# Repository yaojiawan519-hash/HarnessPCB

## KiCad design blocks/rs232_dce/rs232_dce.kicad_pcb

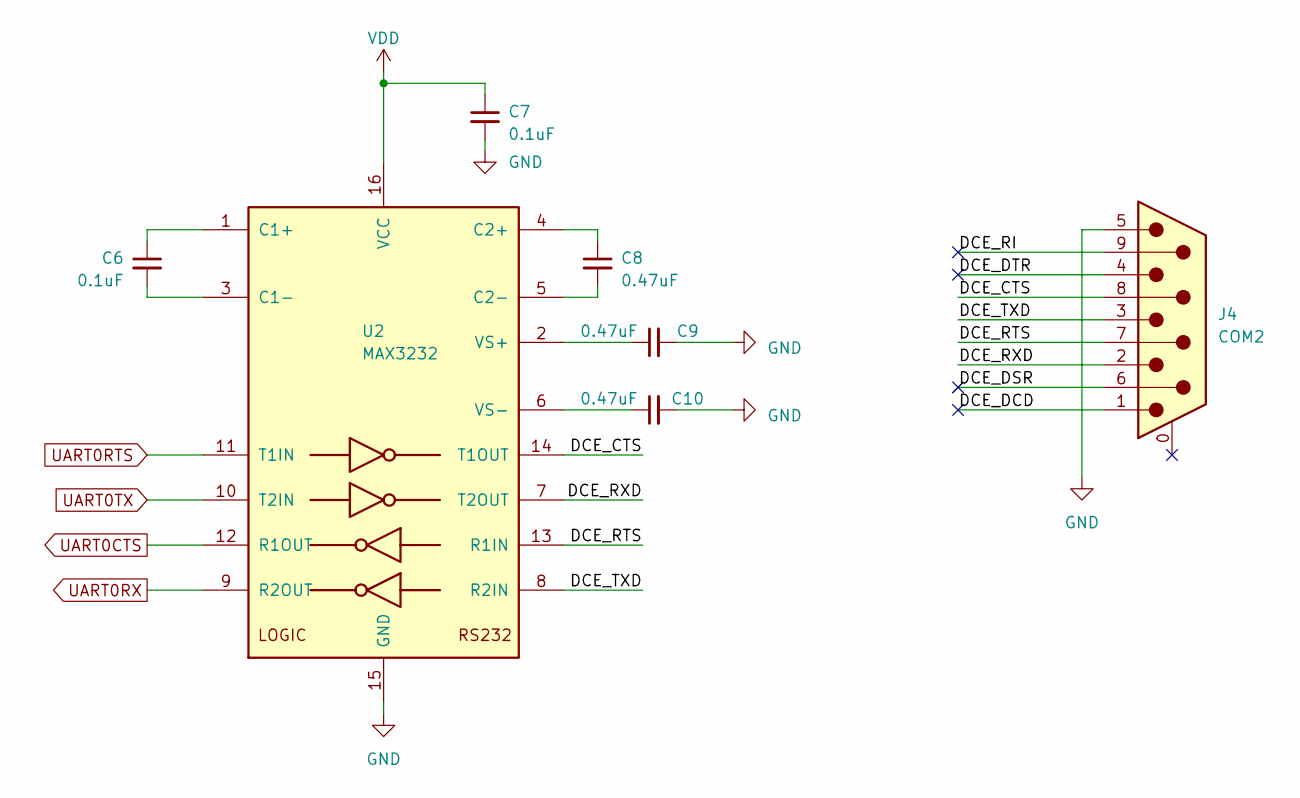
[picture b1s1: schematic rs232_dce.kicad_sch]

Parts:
C6, C7: 0.1uF; C_0805_2012Metric
C8, C9, C10: 0.47uF; C_0805_2012Metric
J4: COM2; DSUB-9_Female_Horizontal_P2.77x2.84mm_EdgePinOffset7.70mm_H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
U2: MAX3232; SOP-16_3.9x9.9mm_P1.27mm

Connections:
/DCE_CTS: J4.8, U2.14 (T1OUT)
/DCE_DCD: J4.1
/DCE_DSR: J4.6
/DCE_DTR: J4.4
/DCE_RI: J4.9
/DCE_RTS: J4.7, U2.13 (R1IN)
/DCE_RXD: J4.2, U2.7 (T2OUT)
/DCE_TXD: J4.3, U2.8 (R2IN)
GND: C7.2, C9.2, C10.2, J4.5, U2.15 (GND)
unnamed: C6.1, U2.1 (C1+)
unnamed: C6.2, U2.3 (C1-)
unnamed: C8.1, U2.4 (C2+)
unnamed: C8.2, U2.5 (C2-)
unnamed: C9.1, U2.2 (VS+)
unnamed: C10.1, U2.6 (VS-)
UART0CTS: U2.12 (R1OUT)
UART0RTS: U2.11 (T1IN)
UART0RX: U2.9 (R2OUT)
UART0TX: U2.10 (T2IN)
VOUT: C7.1, U2.16 (VCC)

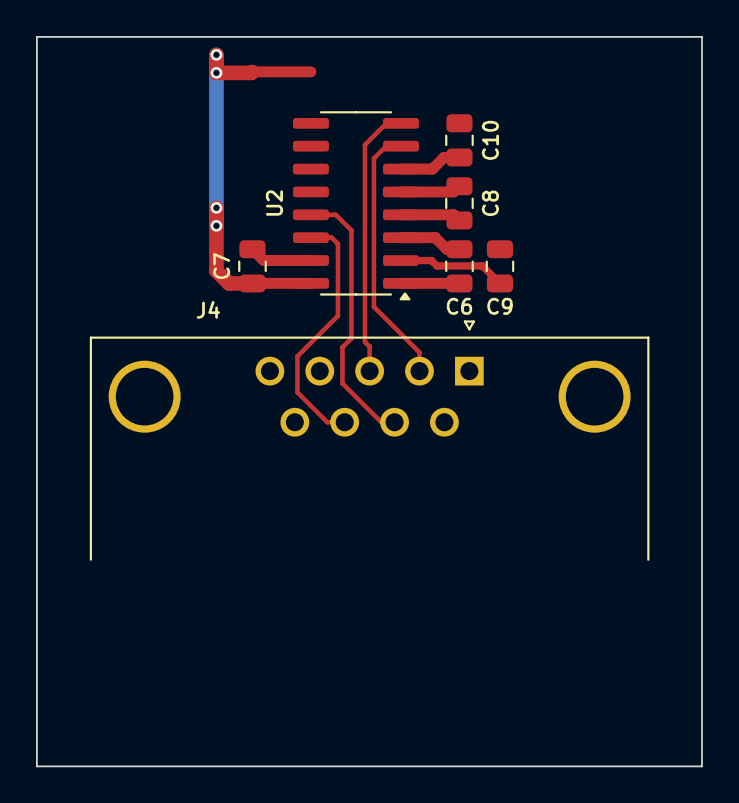
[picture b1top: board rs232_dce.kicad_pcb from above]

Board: 2 copper layers, 37.0 x 40.5 mm, 7 parts (0 on the bottom side), 12 nets.

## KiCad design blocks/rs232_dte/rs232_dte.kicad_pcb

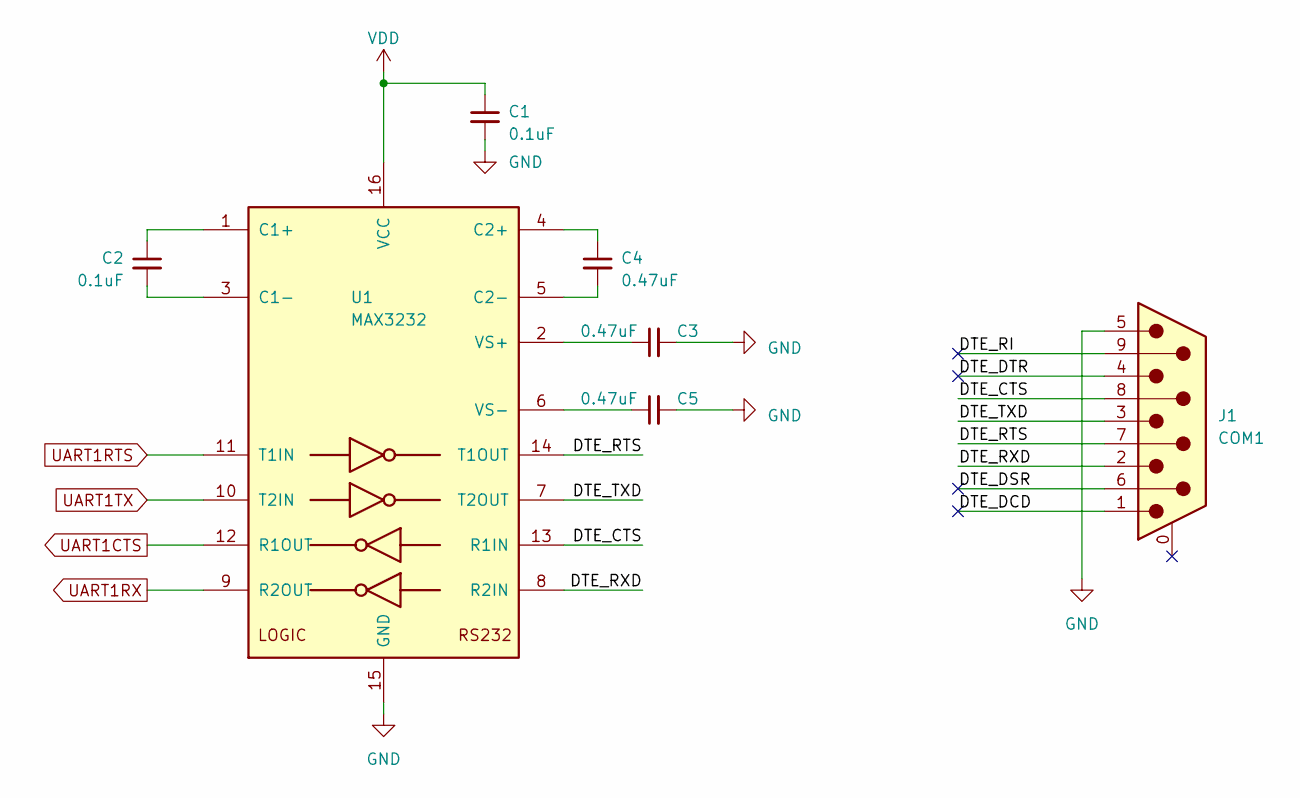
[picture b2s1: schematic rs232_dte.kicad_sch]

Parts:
C1, C2: 0.1uF; C_0805_2012Metric
C3, C4, C5: 0.47uF; C_0805_2012Metric
J1: COM1; DSUB-9_Male_Horizontal_P2.77x2.84mm_EdgePinOffset7.70mm_Hou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
U1: MAX3232; SOP-16_3.9x9.9mm_P1.27mm

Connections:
/DTE_CTS: J1.8, U1.13 (R1IN)
/DTE_DCD: J1.1
/DTE_DSR: J1.6
/DTE_DTR: J1.4
/DTE_RI: J1.9
/DTE_RTS: J1.7, U1.14 (T1OUT)
/DTE_RXD: J1.2, U1.8 (R2IN)
/DTE_TXD: J1.3, U1.7 (T2OUT)
GND: C1.2, C3.2, C5.2, J1.5, U1.15 (GND)
unnamed: C2.1, U1.1 (C1+)
unnamed: C2.2, U1.3 (C1-)
unnamed: C4.1, U1.4 (C2+)
unnamed: C4.2, U1.5 (C2-)
unnamed: C3.1, U1.2 (VS+)
unnamed: C5.1, U1.6 (VS-)
UART1CTS: U1.12 (R1OUT)
UART1RTS: U1.11 (T1IN)
UART1RX: U1.9 (R2OUT)
UART1TX: U1.10 (T2IN)
VOUT: C1.1, U1.16 (VCC)

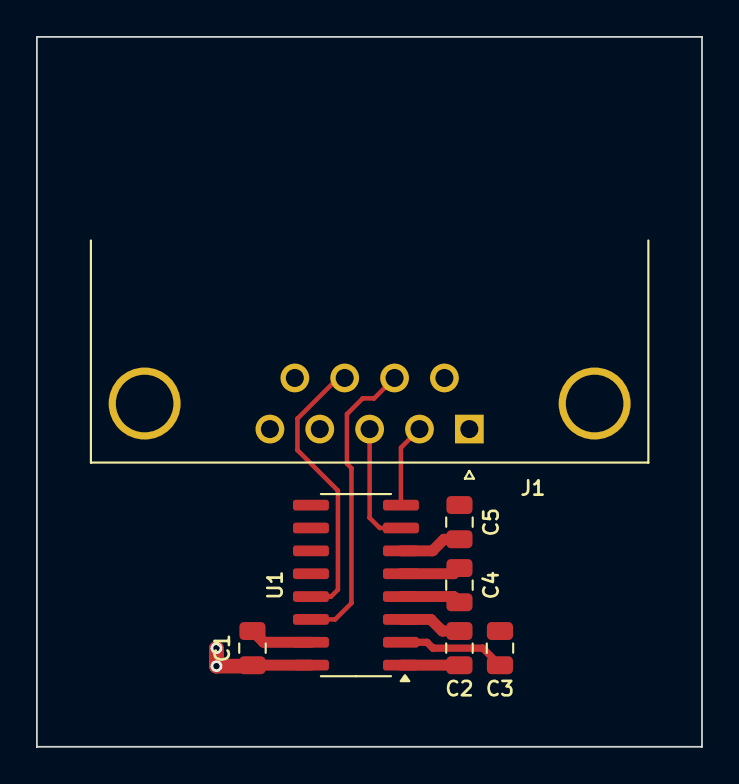
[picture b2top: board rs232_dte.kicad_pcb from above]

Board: 2 copper layers, 37.0 x 39.4 mm, 7 parts (0 on the bottom side), 12 nets.

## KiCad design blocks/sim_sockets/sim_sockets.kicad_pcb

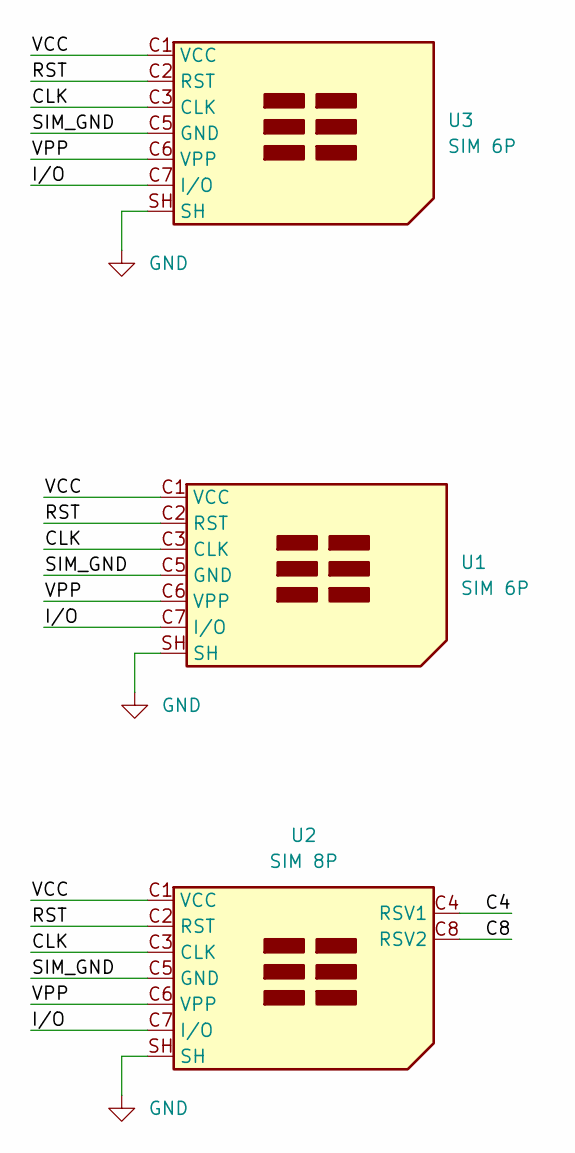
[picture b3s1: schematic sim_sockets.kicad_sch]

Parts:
U1: SIM 6P; DGLZ-SIM-0004
U2: SIM 8P; SIM-0030
U3: SIM 6P; SIM-0036

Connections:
/C4: U2.C4 (RSV1)
/C8: U2.C8 (RSV2)
/CLK: U1.C3 (CLK), U2.C3 (CLK), U3.C3 (CLK)
/I/O: U1.C7 (I/O), U2.C7 (I/O), U3.C7 (I/O)
/RST: U1.C2 (RST), U2.C2 (RST), U3.C2 (RST)
/SIM_GND: U1.C5 (GND), U2.C5 (GND), U3.C5 (GND)
/VCC: U1.C1 (VCC), U2.C1 (VCC), U3.C1 (VCC)
/VPP: U1.C6 (VPP), U2.C6 (VPP), U3.C6 (VPP)
GND: U1.SH, U2.SH, U3.SH

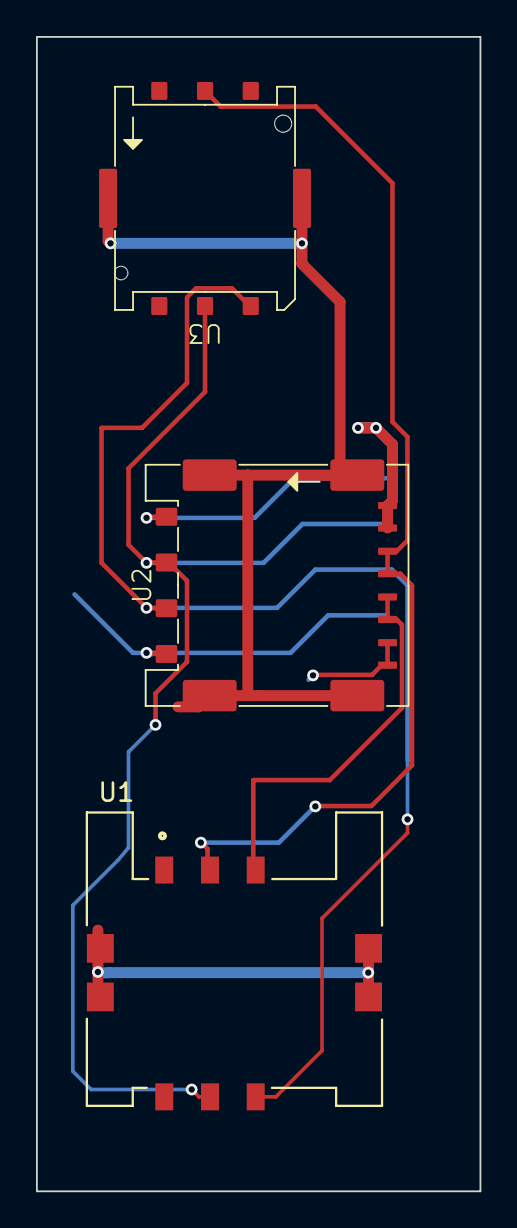
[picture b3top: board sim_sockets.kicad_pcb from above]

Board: 2 copper layers, 24.6 x 64.1 mm, 3 parts (0 on the bottom side), 7 nets.
